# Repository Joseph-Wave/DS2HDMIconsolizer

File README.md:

## DS to HDMI converter

Here is an archive project of mine. It takes the raw video signals of the ds and scale up, pixel to pixel to DVI video in 1080p, 720p, etc. using an artix 7 FPGA (Cmod A7), and play both DS and GBA games.

Demotration can be seen at https://youtube.com/shorts/DusmrjSz5Js

Also share the PCB designs and pinout probing done in the ds family systems (LS030.xlsx), for which the DSi XL is electrically compatible and a second PCB and enclosure were desinged. 
The TFP410 TMDS transmitter and logic buffers are not required in most cases.

Some test roms are included. These are particulary coded to indentify the timing of the 5 bit RGB signals without expensive logic analizer, a cheap off-brand usb 8 Channels is enough.

The future plan was to pass the project to a Tang Primer 25K, a cheaper FPGA, or a dedicaded TFP410 Serializer. But never get the time and money to realize them. I share this in case someone had the same vision...
For more on the DVI serialization see: https://github.com/projf/display_controller

The show scale correspont to a x5.

Here is a drawing of the expectated case using a DSi XL screen and a DS Fat motherboard (this model allow easier wiring as both screen data is recived for both displays, only with differing in the clock signal phase)

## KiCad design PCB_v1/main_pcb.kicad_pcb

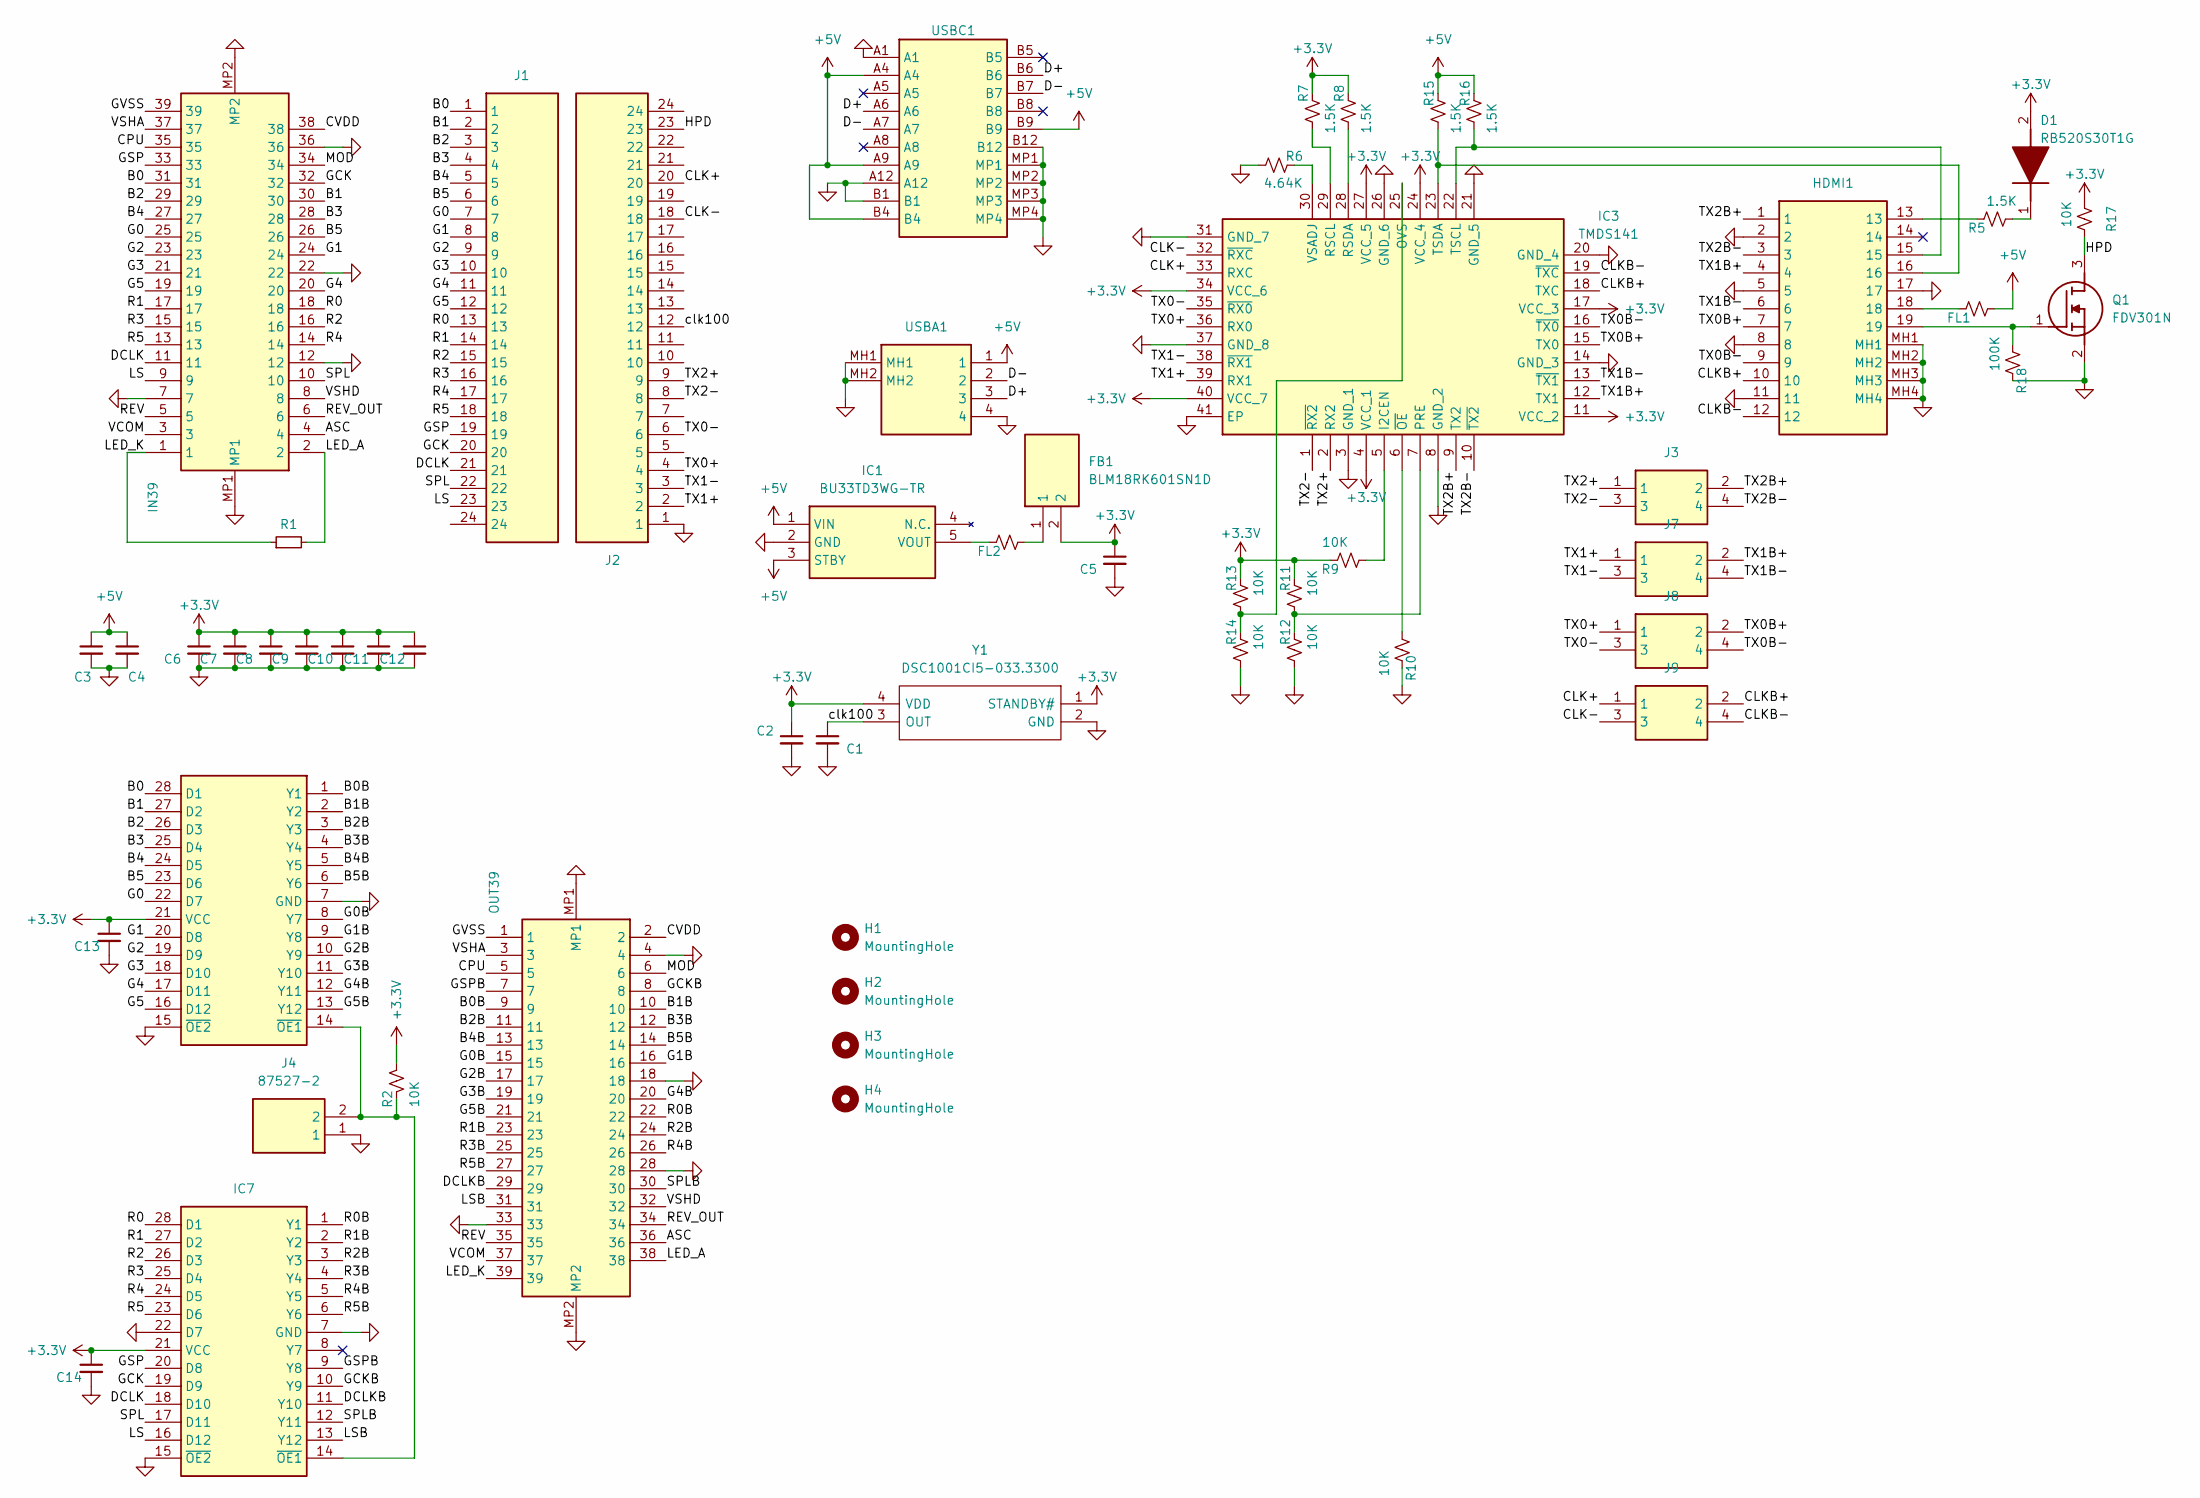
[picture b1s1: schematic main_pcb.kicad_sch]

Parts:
C1, C2, C3, C4, C5, C6, C7, C8, C9, C10, C11, C12, C13, C14: C_Small; C_0201_0603Metric
D1: RB520S30T1G; SODFL1608X70N; Mouser Part Number 863-RB520S30T1G
FB1: BLM18RK601SN1D; BLM18SP221SN1B; Mouser Part Number 81-BLM18RK601SN1
FL1, FL2: 10K; R_1206_3216Metric
H1, H2, H3, H4: MountingHole; MountingHole_2.2mm_M2_Pad_TopBottom
HDMI1: 208658-1051; 2086581051; Mouser Part Number 538-208658-1051
IC1: BU33TD3WG-TR; SOT95P280X125-5N; Mouser Part Number 755-BU33TD3WG-TR
IC3: TMDS141; QFN50P600X600X100-41N-D; Mouser Part Number 595-TMDS141RHAR
IC6, IC7: SN74ABT5402ADWR; SOIC127P1030X265-28N; Mouser Part Number 595-SN74ABT5402ADWR
IN39: 3-2328724-9; 323287249; Mouser Part Number 571-3-2328724-9
J1, J2: 929850-01-24-RA; RHDR24W76P0X254_1X24_6096X254X826P; Mouser Part Number 517-929850-01-24-RA
J3, J7, J8, J9: 826632-2; HDRV4W85P254_2X2_508X500X970P; Mouser Part Number 571-826632-2
J4: 87527-2; HDRV2W66P0X254_1X2_467X244X1044P; Mouser Part Number 571-875272
OUT39: 3-2328724-9; 323287249; Mouser Part Number 571-3-2328724-9
Q1: FDV301N; SOT96P237X111-3N; Mouser Part Number 512-FDV301N
R1: R_Small; R_Axial_DIN0207_L6.3mm_D2.5mm_P7.62mm_Horizontal
R2, R9, R10, R11, R12, R13, R14, R17: 10K; R_0201_0603Metric
R5, R7, R8, R15, R16: 1.5K; R_0201_0603Metric
R6: 4.64K; R_0201_0603Metric
R18: 100K; R_0201_0603Metric
USBA1: 1734366-2; 17343662; Mouser Part Number 571-1734366-2
USBC1: USB4110-GF-A; USB4110GFA; Mouser Part Number 640-USB4110-GF-A
Y1: DSC1001CI5-033.3300; DSC1001CI50333300; Mouser Part Number 579-SC1001CI50333300

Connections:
+5V: C3.1, C4.1, FL1.1, IC1.1 (VIN), IC1.3 (STBY), R15.2, R16.2, USBA1.1, USBC1.A4, USBC1.A9, USBC1.B4, USBC1.B9
/ASC: IN39.4, OUT39.36
/B0: IC6.28 (D1), IN39.31, J1.1
/B0B: IC6.1 (Y1), OUT39.9
/B1: IC6.27 (D2), IN39.30, J1.2
/B1B: IC6.2 (Y2), OUT39.10
/B2: IC6.26 (D3), IN39.29, J1.3
/B2B: IC6.3 (Y3), OUT39.11
/B3: IC6.25 (D4), IN39.28, J1.4
/B3B: IC6.4 (Y4), OUT39.12
/B4: IC6.24 (D5), IN39.27, J1.5
/B4B: IC6.5 (Y5), OUT39.13
/B5: IC6.23 (D6), IN39.26, J1.6
/B5B: IC6.6 (Y6), OUT39.14
/CLK+: IC3.33 (RXC), J2.20, J9.1
/CLK-: IC3.32 (~RXC), J2.18, J9.3
/CLKB+: HDMI1.10, IC3.18 (TXC), J9.2
/CLKB-: HDMI1.12, IC3.19 (~TXC), J9.4
/CPU: IN39.35, OUT39.5
/CVDD: IN39.38, OUT39.2
/D+: USBA1.3, USBC1.A6, USBC1.B6
/D-: USBA1.2, USBC1.A7, USBC1.B7
/DCLK: IC7.18 (D10), IN39.11, J1.21
/DCLKB: IC7.11 (Y10), OUT39.29
/G0: IC6.22 (D7), IN39.25, J1.7
/G0B: IC6.8 (Y7), OUT39.15
/G1: IC6.20 (D8), IN39.24, J1.8
/G1B: IC6.9 (Y8), OUT39.16
/G2: IC6.19 (D9), IN39.23, J1.9
/G2B: IC6.10 (Y9), OUT39.17
/G3: IC6.18 (D10), IN39.21, J1.10
/G3B: IC6.11 (Y10), OUT39.19
/G4: IC6.17 (D11), IN39.20, J1.11
/G4B: IC6.12 (Y11), OUT39.20
/G5: IC6.16 (D12), IN39.19, J1.12
/G5B: IC6.13 (Y12), OUT39.21
/GCK: IC7.19 (D9), IN39.32, J1.20
/GCKB: IC7.10 (Y9), OUT39.8
/GSP: IC7.20 (D8), IN39.33, J1.19
/GSPB: IC7.9 (Y8), OUT39.7
/GVSS: IN39.39, OUT39.1
/HPD: J2.23, Q1.3 (D), R17.2
/LED_A: IN39.2, OUT39.38, R1.2; also elsewhere on the board
/LED_K: IN39.1, OUT39.39, R1.1; also elsewhere on the board
/LS: IC7.16 (D12), IN39.9, J1.23
/LSB: IC7.13 (Y12), OUT39.31
/MOD: IN39.34, OUT39.6
/R0: IC7.28 (D1), IN39.18, J1.13
/R0B: IC7.1 (Y1), OUT39.22
/R1: IC7.27 (D2), IN39.17, J1.14
/R1B: IC7.2 (Y2), OUT39.23
/R2: IC7.26 (D3), IN39.16, J1.15
/R2B: IC7.3 (Y3), OUT39.24
/R3: IC7.25 (D4), IN39.15, J1.16
/R3B: IC7.4 (Y4), OUT39.25
/R4: IC7.24 (D5), IN39.14, J1.17
/R4B: IC7.5 (Y5), OUT39.26
/R5: IC7.23 (D6), IN39.13, J1.18
/R5B: IC7.6 (Y6), OUT39.27
/REV: IN39.5, OUT39.35
/REV_OUT: IN39.6, OUT39.34
/SPL: IC7.17 (D11), IN39.10, J1.22
/SPLB: IC7.12 (Y11), OUT39.30
/TX0+: IC3.36 (RX0), J2.4, J8.1
/TX0-: IC3.35 (~RX0), J2.6, J8.3
/TX0B+: HDMI1.7, IC3.15 (TX0), J8.2
/TX0B-: HDMI1.9, IC3.16 (~TX0), J8.4
/TX1+: IC3.39 (RX1), J2.2, J7.1
/TX1-: IC3.38 (~RX1), J2.3, J7.3
/TX1B+: HDMI1.4, IC3.12 (TX1), J7.2
/TX1B-: HDMI1.6, IC3.13 (~TX1), J7.4
/TX2+: IC3.2 (RX2), J2.9, J3.1
/TX2-: IC3.1 (~RX2), J2.8, J3.3
/TX2B+: HDMI1.1, IC3.9 (TX2), J3.2
/TX2B-: HDMI1.3, IC3.10 (~TX2), J3.4
/VCOM: IN39.3, OUT39.37
/VSHA: IN39.37, OUT39.3
/VSHD: IN39.8, OUT39.32
/clk100: C1.1, J2.12, Y1.3 (OUT)
unnamed: D1.1 (K), R5.1
unnamed: FB1.1, FL2.1
unnamed: FL1.2, HDMI1.18
unnamed: HDMI1.13, R5.2
unnamed: FL2.2, IC1.5 (VOUT)
unnamed: IC3.5 (I2CEN), R9.1
unnamed: IC3.25 (OVS), R13.1, R14.2
unnamed: IC3.7 (PRE), R11.1, R12.2
unnamed: IC3.29 (RSCL), R7.1
unnamed: IC3.28 (RSDA), R8.1
unnamed: HDMI1.15, IC3.22 (TSCL), R16.1
unnamed: HDMI1.16, IC3.23 (TSDA), R15.1
unnamed: IC3.30 (VSADJ), R6.2
unnamed: IC3.6 (~OE), R10.1
unnamed: HDMI1.19, Q1.1 (G), R18.1

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
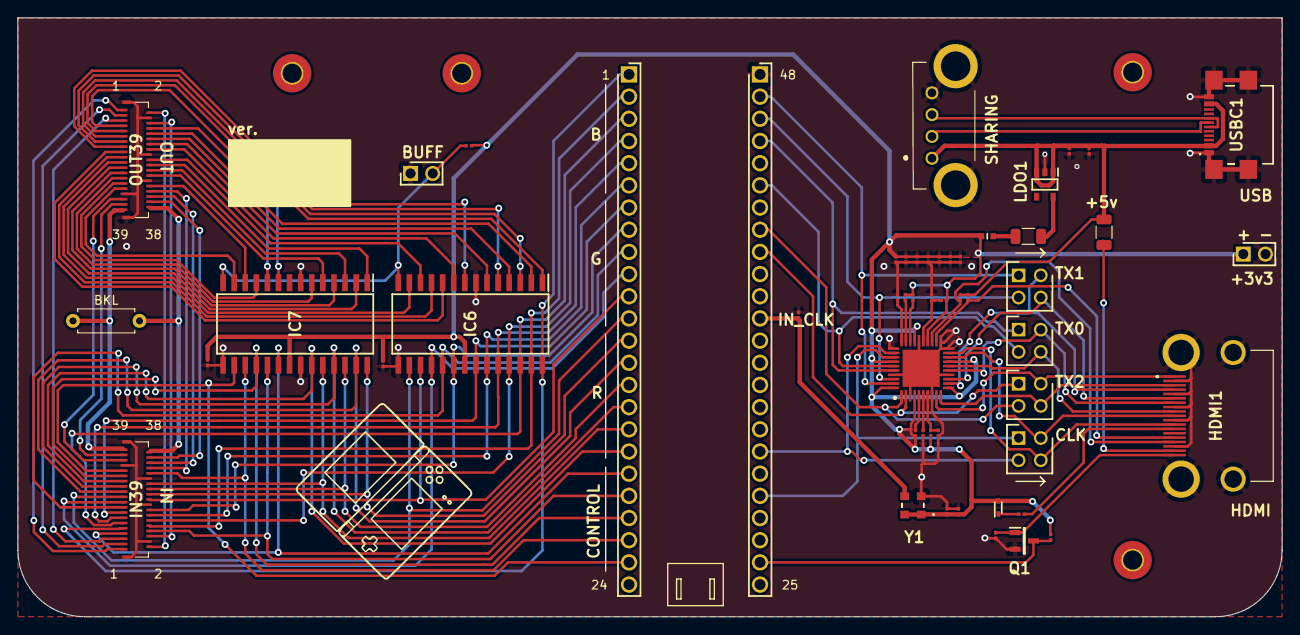
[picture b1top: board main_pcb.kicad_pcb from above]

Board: 2 copper layers, 144.8 x 68.6 mm, 57 parts (0 on the bottom side), 97 nets.

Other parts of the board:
BKL: R_Small; R_Axial_DIN0207_L6.3mm_D2.5mm_P7.62mm_Horizontal
J4#2: 87527-2; HDRV2W66P0X254_1X2_467X244X1044P

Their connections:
/LED_A: BKL.2; also elsewhere on the board
/LED_K: BKL.1; also elsewhere on the board
